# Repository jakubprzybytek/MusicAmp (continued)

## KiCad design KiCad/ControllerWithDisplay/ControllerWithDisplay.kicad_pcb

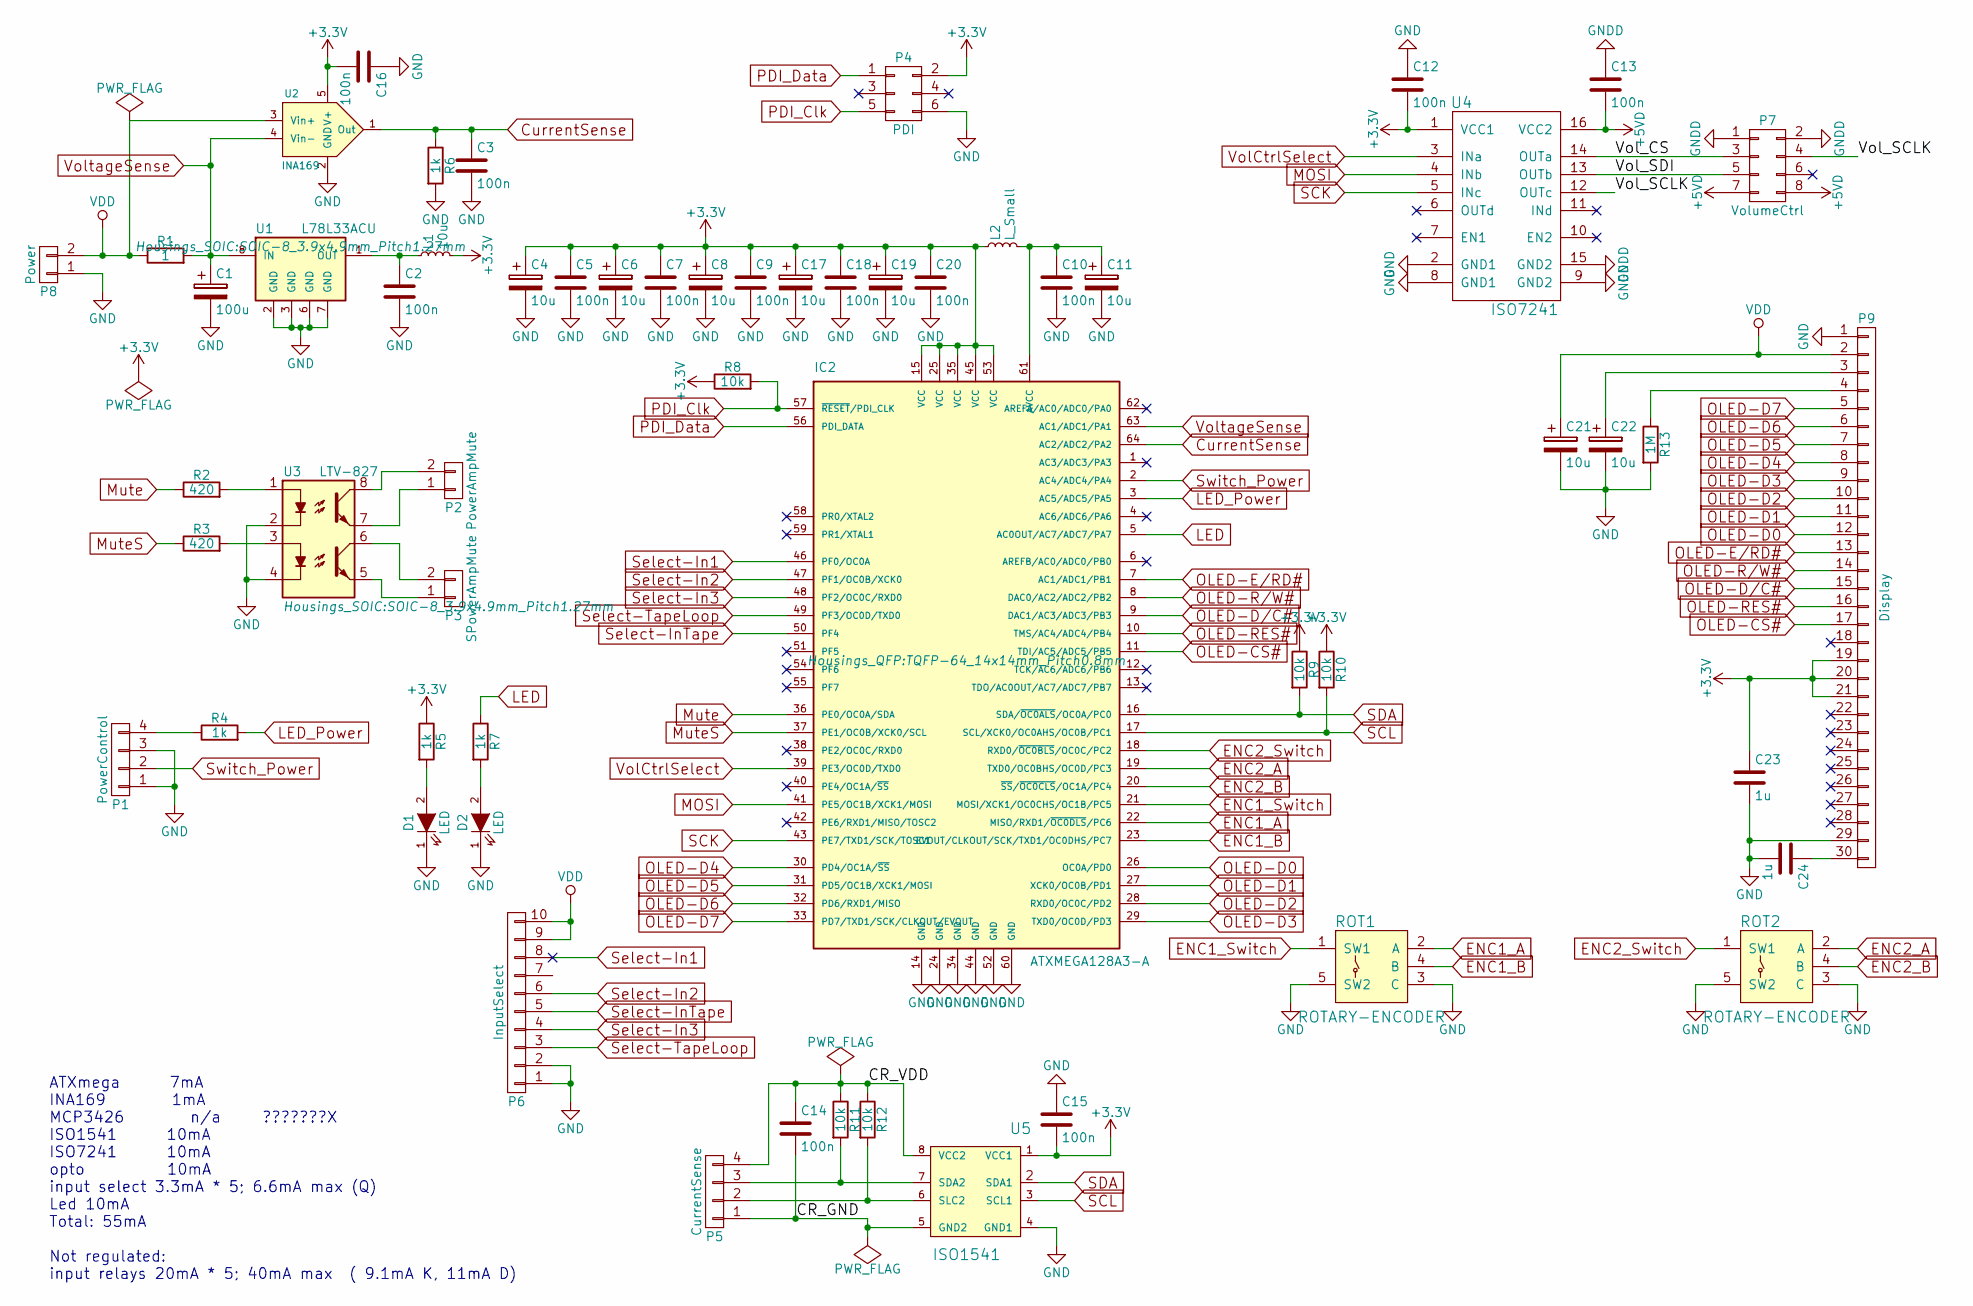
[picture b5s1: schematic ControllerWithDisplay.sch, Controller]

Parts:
C1: 100u; C_Radial_D5_L6_P2.5
C2, C3, C5, C7, C9, C10, C12, C13, C14, C15, C16, C18, C20: 100n; C_0805
C4, C6, C8, C11, C17, C19: 10u; C_Radial_D5_L6_P2.5
C21, C22: 10u; c_elec_4x5.8
C23, C24: 1u; C_0805
D1, D2: LED; LED_0805
IC2: ATXMEGA128A3-A; TQFP-64_14x14mm_Pitch0.8mm
L1: 10u; Choke_SMD_1206_Standard
L2: L_Small; Choke_SMD_1206_Standard
P1: PowerControl; Pin_Header_Angled_1x04
P2: PowerAmpMute; Pin_Header_Angled_1x02
P3: SPowerAmpMute; Pin_Header_Angled_1x02
P4: PDI; Pin_Header_Straight_2x03
P5: CurrentSense; Pin_Header_Angled_1x04
P6: InputSelect; Pin_Header_Angled_2x05
P7: VolumeCtrl; Pin_Header_Angled_2x04
P8: Power; Pin_Header_Angled_1x02
P9: Display; FPC_30
R1: 1; R_1206_HandSoldering
R2, R3: 420; R_0805
R4, R5, R6, R7: 1k; R_0805
R8, R9, R10, R11, R12: 10k; R_0805
R13: 1M; R_0805
ROT1, ROT2: ROTARY-ENCODER; SF-ROTARY-ENCODER
U1: L78L33ACU; SOIC-8_3.9x4.9mm_Pitch1.27mm
U2: INA169; SOT-23-5
U3: LTV-827; SOIC-8_3.9x4.9mm_Pitch1.27mm
U4: ISO7241; SOIC-16_3.9x9.9mm_Pitch1.27mm
U5: ISO1541; SOIC-8_3.9x4.9mm_Pitch1.27mm

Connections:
+3V3: C4.1, C5.1, C6.1, C7.1, C8.1, C9.1, C12.2, C15.2, C16.2, C17.1, C18.1, C19.1, C20.1, C23.1, IC2.15 (VCC), IC2.25 (VCC), IC2.35 (VCC), IC2.45 (VCC), IC2.53 (VCC), L1.2, L2.1, P4.2, P9.19, P9.20, P9.21, R5.1, R8.1, R9.1, R10.1, U2.5 (V+), U4.1 (VCC1), U5.1 (VCC1)
+5VD: C13.2, P7.7, P7.8, U4.16 (VCC2)
/CR_GND: C14.2, P5.1, U5.5 (GND2)
/CR_VDD: C14.1, P5.4, R11.1, R12.1, U5.8 (VCC2)
/Vol_CS: P7.3, U4.14 (OUTa)
/Vol_SCLK: P7.4, U4.12 (OUTc)
/Vol_SDI: P7.5, U4.13 (OUTb)
CurrentSense: C3.1, IC2.64 (AC2/ADC2/PA2), R6.1, U2.1 (Out)
ENC1_A: IC2.22 (MISO/RXD1/~OC0DLS~/PC6), ROT1.2 (A)
ENC1_B: IC2.23 (EVOUT/CLKOUT/SCK/TXD1/OC0DHS/PC7), ROT1.4 (B)
ENC1_Switch: IC2.21 (MOSI/XCK1/OC0CHS/OC1B/PC5), ROT1.1 (SW1)
ENC2_A: IC2.19 (TXD0/OC0BHS/OC0D/PC3), ROT2.2 (A)
ENC2_B: IC2.20 (~SS~/~OC0CLS~/OC1A/PC4), ROT2.4 (B)
ENC2_Switch: IC2.18 (RXD0/~OC0BLS~/OC0C/PC2), ROT2.1 (SW1)
GND: C1.2, C2.2, C3.2, C4.2, C5.2, C6.2, C7.2, C8.2, C9.2, C10.2, C11.2, C12.1, C15.1, C16.1, C17.2, C18.2, C19.2, C20.2, C21.2, C22.2, C23.2, C24.2, D1.1 (K), D2.1 (K), IC2.14 (GND), IC2.24 (GND), IC2.34 (GND), IC2.44 (GND), IC2.52 (GND), IC2.60 (GND), P1.1, P1.3, P4.6, P6.1, P6.2, P8.1, P9.1, P9.29, R6.2, R13.2, ROT1.3 (C), ROT1.5 (SW2), ROT2.3 (C), ROT2.5 (SW2), U1.2 (GND), U1.3 (GND), U1.6 (GND), U1.7 (GND), U2.2 (GND), U3.2, U3.4, U4.2 (GND1), U4.8 (GND1), U5.4 (GND1)
GNDD: C13.1, P7.1, P7.2, U4.9 (GND2), U4.15 (GND2)
LED: IC2.5 (AC0OUT/AC7/ADC7/PA7), R7.1
LED_Power: IC2.3 (AC5/ADC5/PA5), R4.2
MOSI: IC2.41 (PE5/OC1B/XCK1/MOSI), U4.4 (INb)
Mute: IC2.36 (PE0/OC0A/SDA), R2.1
MuteS: IC2.37 (PE1/OC0B/XCK0/SCL), R3.1
unnamed: C2.1, L1.1, U1.1 (OUT)
unnamed: C10.1, C11.1, IC2.61 (AVCC), L2.2
unnamed: C22.1, P9.3
unnamed: C24.1, P9.30
unnamed: D1.2 (A), R5.2
unnamed: D2.2 (A), R7.2
unnamed: P1.4, R4.1
unnamed: P2.1, U3.7
unnamed: P2.2, U3.8
unnamed: P3.1, U3.5
unnamed: P3.2, U3.6
unnamed: P5.2, R12.2, U5.6 (SLC2)
unnamed: P5.3, R11.2, U5.7 (SDA2)
unnamed: P9.4, R13.1
unnamed: R2.2, U3.1
unnamed: R3.2, U3.3
OLED-CS#: IC2.11 (TDI/AC5/ADC5/PB5), P9.17
OLED-D0: IC2.26 (OC0A/PD0), P9.12
OLED-D1: IC2.27 (XCK0/OC0B/PD1), P9.11
OLED-D2: IC2.28 (RXD0/OC0C/PD2), P9.10
OLED-D3: IC2.29 (TXD0/OC0D/PD3), P9.9
OLED-D4: IC2.30 (PD4/OC1A/~SS~), P9.8
OLED-D5: IC2.31 (PD5/OC1B/XCK1/MOSI), P9.7
OLED-D6: IC2.32 (PD6/RXD1/MISO), P9.6
OLED-D7: IC2.33 (PD7/TXD1/SCK/CLKOUT/EVOUT), P9.5
OLED-D/C#: IC2.9 (DAC1/AC3/ADC3/PB3), P9.15
OLED-E/RD#: IC2.7 (AC1/ADC1/PB1), P9.13
OLED-R/W#: IC2.8 (DAC0/AC2/ADC2/PB2), P9.14
OLED-RES#: IC2.10 (TMS/AC4/ADC4/PB4), P9.16
PDI_Clk: IC2.57 (~RESET~/PDI_CLK), P4.5, R8.2
PDI_Data: IC2.56 (PDI_DATA), P4.1
SCK: IC2.43 (PE7/TXD1/SCK/TOSC1), U4.5 (INc)
SCL: IC2.17 (SCL/XCK0/OC0AHS/OC0B/PC1), R10.2, U5.3 (SCL1)
SDA: IC2.16 (SDA/~OC0ALS~/OC0A/PC0), R9.2, U5.2 (SDA1)
Select-In1: IC2.46 (PF0/OC0A), P6.8
Select-In2: IC2.47 (PF1/OC0B/XCK0), P6.6
Select-In3: IC2.48 (PF2/OC0C/RXD0), P6.4
Select-InTape: IC2.50 (PF4), P6.5
Select-TapeLoop: IC2.49 (PF3/OC0D/TXD0), P6.3
Switch_Power: IC2.2 (AC4/ADC4/PA4), P1.2
VDD: C21.1, P6.9, P6.10, P8.2, P9.2, R1.1, U2.3 (Vin+)
VolCtrlSelect: IC2.39 (PE3/OC0D/TXD0), U4.3 (INa)
VoltageSense: C1.1, IC2.63 (AC1/ADC1/PA1), R1.2, U1.8 (IN), U2.4 (Vin-)

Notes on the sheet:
ATXmega 7mA INA169 1mA MCP3426 n/a ???????X ISO1541 10mA ISO7241 10mA opto 10mA input select 3.3mA * 5; 6.6mA max (Q) Led 10mA Total: 55mA Not regulated: input relays 20mA * 5; 40mA max ( 9.1mA K, 11mA D)

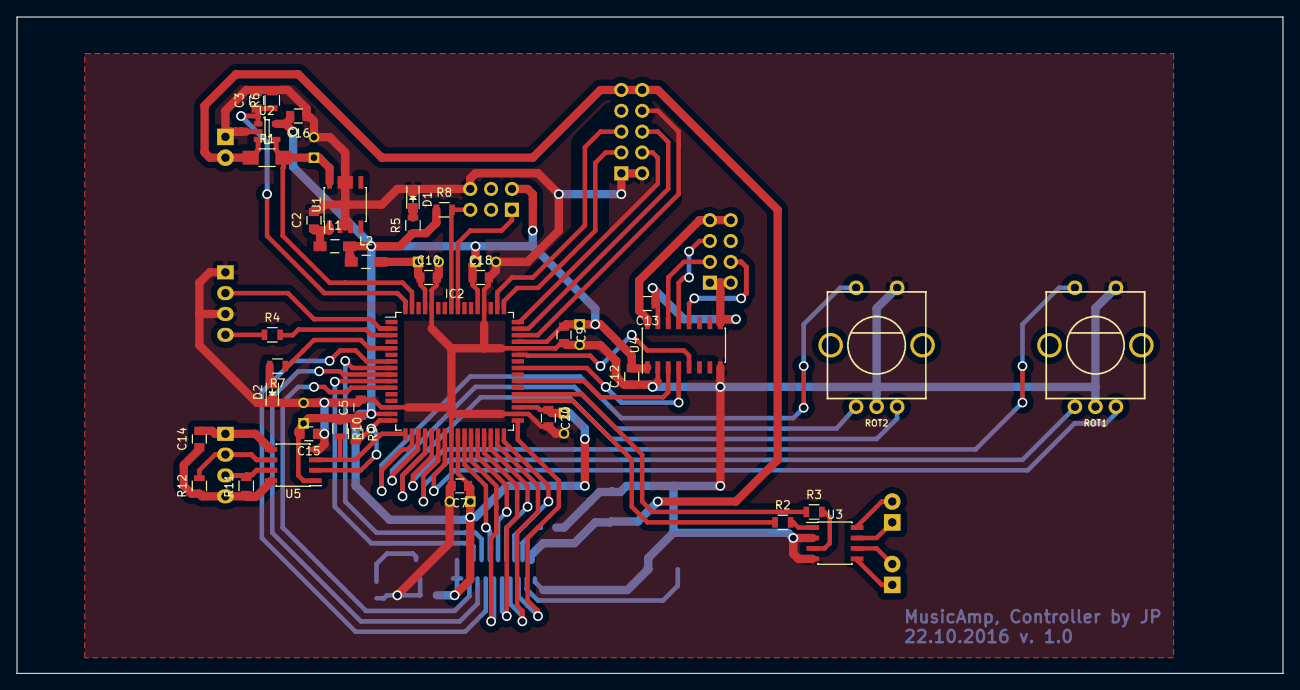
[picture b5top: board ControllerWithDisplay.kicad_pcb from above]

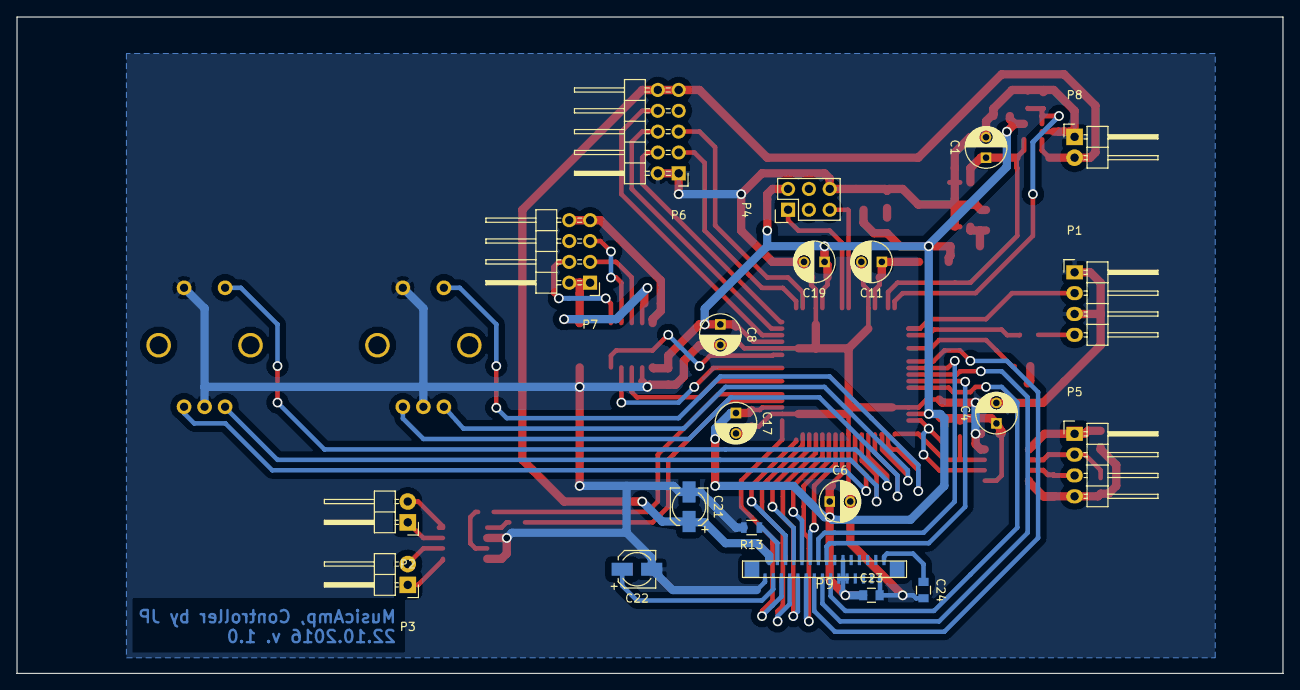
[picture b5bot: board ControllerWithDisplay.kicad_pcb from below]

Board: 2 copper layers, 154.3 x 80.0 mm, 58 parts (21 on the bottom side), 64 nets.

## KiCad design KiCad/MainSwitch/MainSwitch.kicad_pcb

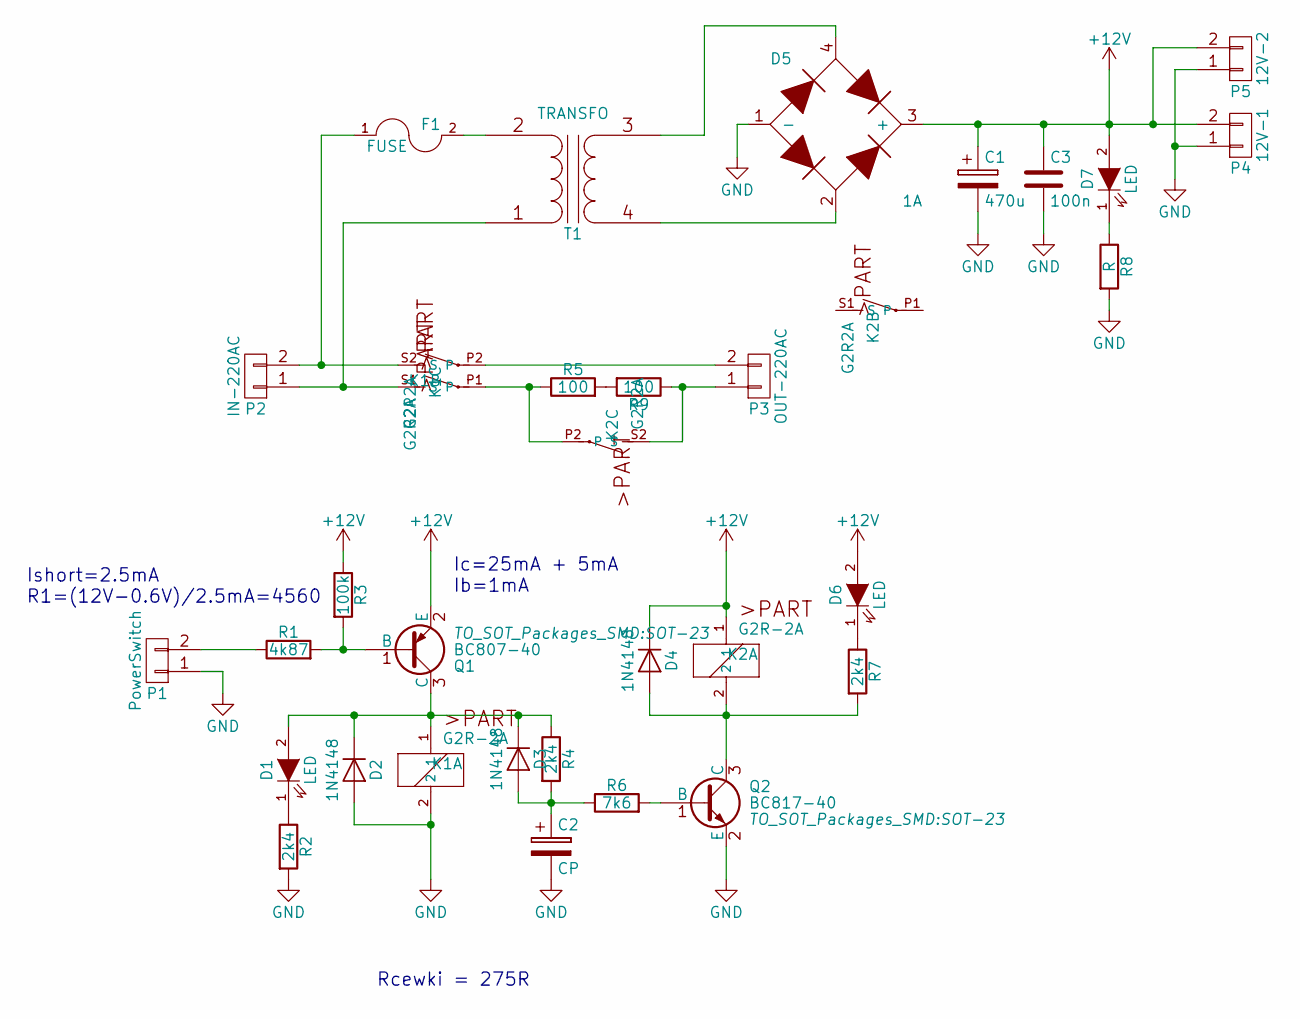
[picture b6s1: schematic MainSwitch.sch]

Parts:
C1: 470u; CP_Radial_D8.0mm_P2.50mm
C2: CP; CP_Radial_D8.0mm_P2.50mm
C3: 100n; C_0805
D1, D6, D7: LED; LED_D5.0mm
D2, D3, D4: 1N4148; D_1206
D5: 1A; RB-15
F1: FUSE; Fuseholder5x20_horiz_open_inline_Type-I
K1, K2: G2R-2A; relay-G2R2A
P1: PowerSwitch; PINHEAD1-2
P2: IN-220AC; Molex_MiniFit-JR-5556-02A_2x01x4.20mm_Straight
P3: OUT-220AC; Molex_MiniFit-JR-5556-02A_2x01x4.20mm_Straight
P4: 12V-1; PINHEAD1-2
P5: 12V-2; PINHEAD1-2
Q1: BC807-40; SOT-23
Q2: BC817-40; SOT-23
R1: 4k87; R_0805
R2, R4, R7: 2k4; R_0805
R3: 100k; R_0805
R5, R9: 100; R_Axial_Power_L48.0mm_W12.5mm_P10.16mm_Vertical
R6: 7k6; R_0805
R8: R; R_0805
T1: TRANSFO; Trafo-1,6-8,11

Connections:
+12V: C1.1, C3.1, D4.1 (K), D5.3 (+), D6.2 (A), D7.2 (A), K2.1, P4.2, P5.2, Q1.2 (E), R3.1
GND: C1.2, C2.2, C3.2, D2.2 (A), D5.1 (-), K1.2, P1.1, P4.1, P5.1, Q2.2 (E), R2.2, R8.2
unnamed: C2.1, D3.2 (A), R4.2, R6.1
unnamed: D1.1 (K), R2.1
unnamed: D1.2 (A), D2.1 (K), D3.1 (K), K1.1, Q1.3 (C), R4.1
unnamed: D4.2 (A), K2.2, Q2.3 (C), R7.2
unnamed: D5.2, T1.4 (SB)
unnamed: D5.4, T1.3 (SA)
unnamed: D6.1 (K), R7.1
unnamed: D7.1 (K), R8.1
unnamed: F1.1, K1.S2 (S), P2.2
unnamed: F1.2, T1.2 (AB)
unnamed: K1.P1, K2.P2, R5.1
unnamed: K1.P2, P3.2
unnamed: K1.S1 (S), P2.1, T1.1 (AA)
unnamed: K2.S2 (S), P3.1, R9.1
unnamed: P1.2, R1.1
unnamed: Q1.1 (B), R1.2, R3.2
unnamed: Q2.1 (B), R6.2
unnamed: R5.2, R9.2

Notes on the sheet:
Rcewki = 275R
Ic=25mA + 5mA Ib=1mA
Ishort=2.5mA R1=(12V-0.6V)/2.5mA=4560

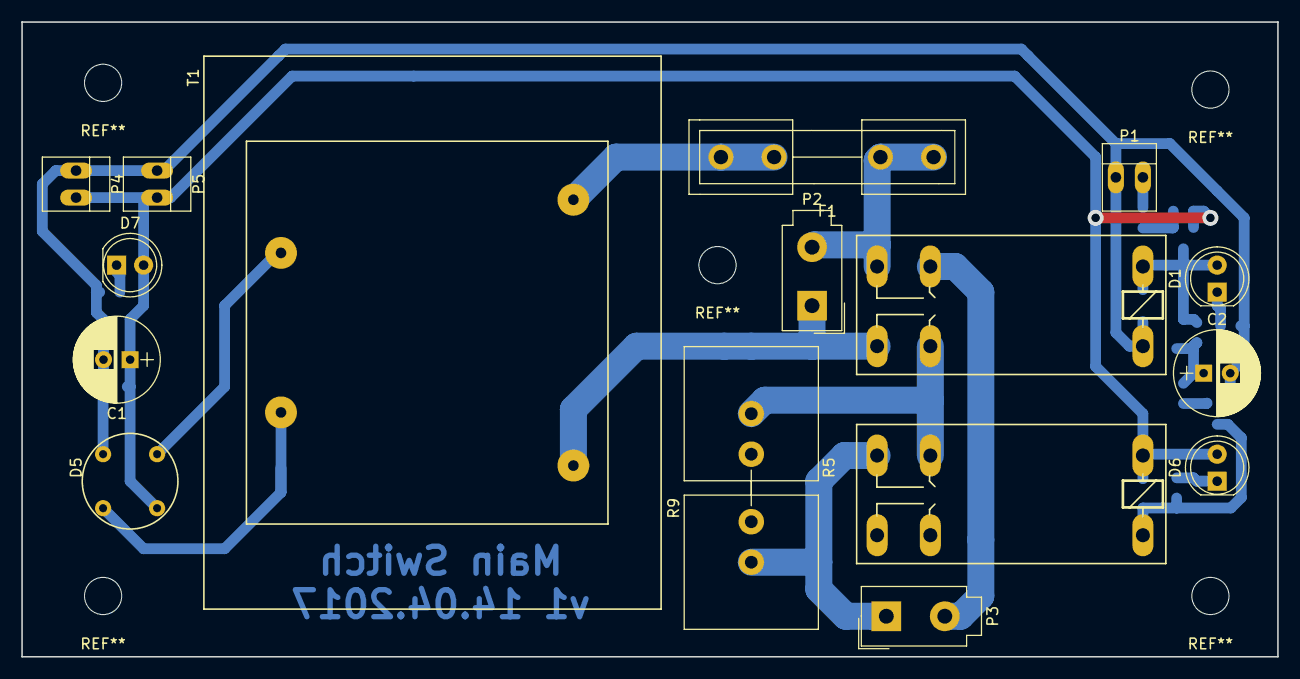
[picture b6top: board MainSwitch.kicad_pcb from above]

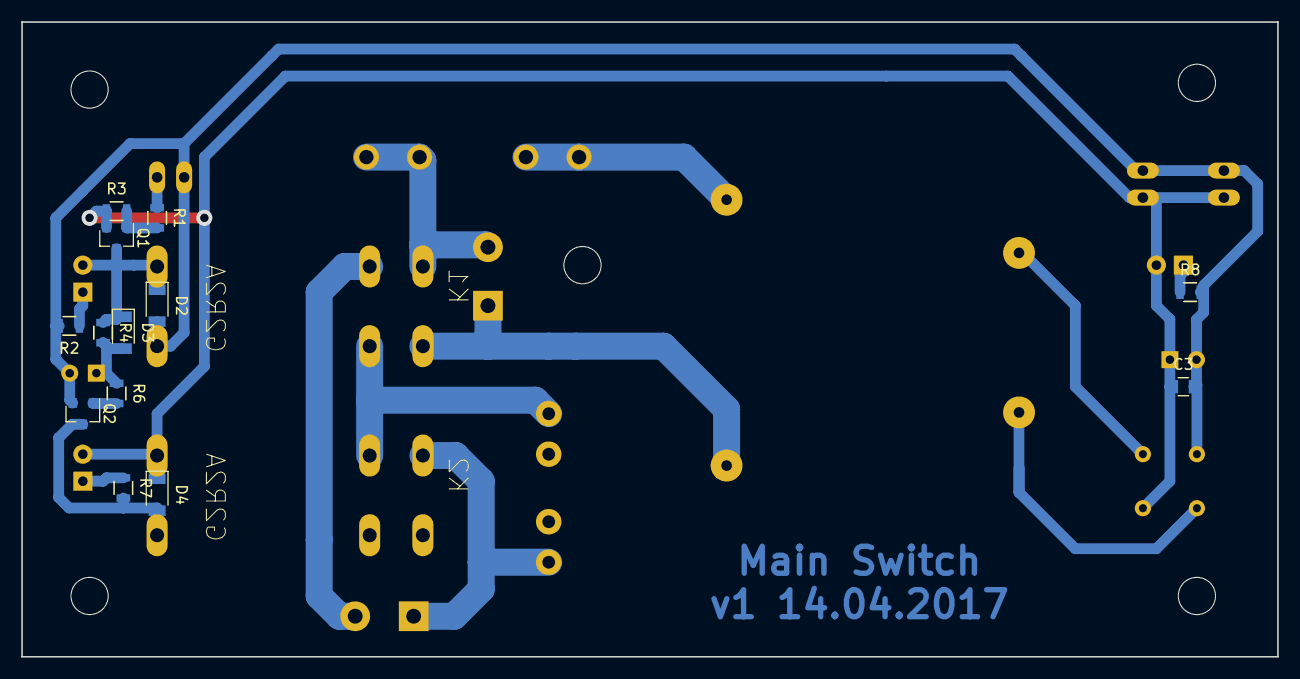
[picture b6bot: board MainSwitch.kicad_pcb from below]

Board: 2 copper layers, 118.1 x 59.7 mm, 30 parts (13 on the bottom side), 20 nets.

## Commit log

2017-06-17 init commit
2017-06-18 encoder
2017-06-29 power switch
2017-07-12 power control
2017-07-12 events
2017-07-13 Common code for switches
2017-07-13 Input selector
2017-07-14 Volume control
2017-07-17 LUFA and MCP3426 ADC
2017-07-17 heartbeat introduced
2017-07-17 files rearrangement
2017-07-30 Displaying power
2017-08-10 Volume controll
2018-04-06 Rearranging files
2018-04-06 Adding KiCad project
2019-05-14 Refresh commit
2019-05-14 clean up
2019-05-14 gitignore update
2019-05-14 Input selector button and tape loop controlls added
2019-05-14 Making encoders disabled when amp is off
2019-05-22 PreAmp PCP pimped
2019-05-23 Last tweaks
2019-05-24 Silk stuff
2019-07-09 Fixes in controller app
2019-07-12 Latest fixes
2019-07-20 Better subwoofer volume control
2019-07-20 Storing settings
2019-07-27 Power Amp board v3
2019-08-31 Small tweaks
